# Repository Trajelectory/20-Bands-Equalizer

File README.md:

# Equalizer 20 Bands avec Vumètre LED

## Description du Projet
Ce projet permet de modifier le son en ajustant les niveaux de fréquence tout en affichant visuellement l'intensité du signal audio via un vumètre LED.

## Fonctionnalités
- **Égaliseur graphique 20 bandes** pour un réglage précis des fréquences audio.
- **Vumètre LED** basé sur un circuit spécialisé pour une visualisation dynamique du signal.
- **Entrée et sortie audio** pour intégration dans des systèmes hi-fi ou de studio.
- **Alimentation stabilisée** pour un fonctionnement optimal et sans bruit.
- **Conception optimisée** avec une séparation des pistes minimisant les interférences.

## Matériel Utilisé
- **Logiciel de conception** : KiCad
- **Composants principaux** :
  - Amplificateurs opérationnels (ex: TL074, TL072)
  - Filtres actifs RC pour le traitement du signal
  - Potentiomètres pour le réglage des bandes
  - Circuit de vumètre
  - LED pour l'affichage du signal
  - Connecteurs audio pour l'entrée/sortie

## Fichiers Inclus
- **Schéma KiCad** : `20 Bands Equalizer.kicad_sch`
- **PCB KiCad** : `20 Bands Equalizer.kicad_pcb`
- **Les fichiers de fabrications compatible JLCPCB`

## Améliorations Possibles
- Ajout d'un **affichage LCD** pour afficher les valeurs des bandes.
- Conception d'un **boîtier imprimé en 3D** pour l'intégration.
- Optimisation de l'alimentation pour **baisser la consommation énergétique**.

## Licence
Ce projet est sous licence **MIT**, ce qui signifie que vous pouvez l'utiliser, le modifier et le partager librement en mentionnant l'auteur original.

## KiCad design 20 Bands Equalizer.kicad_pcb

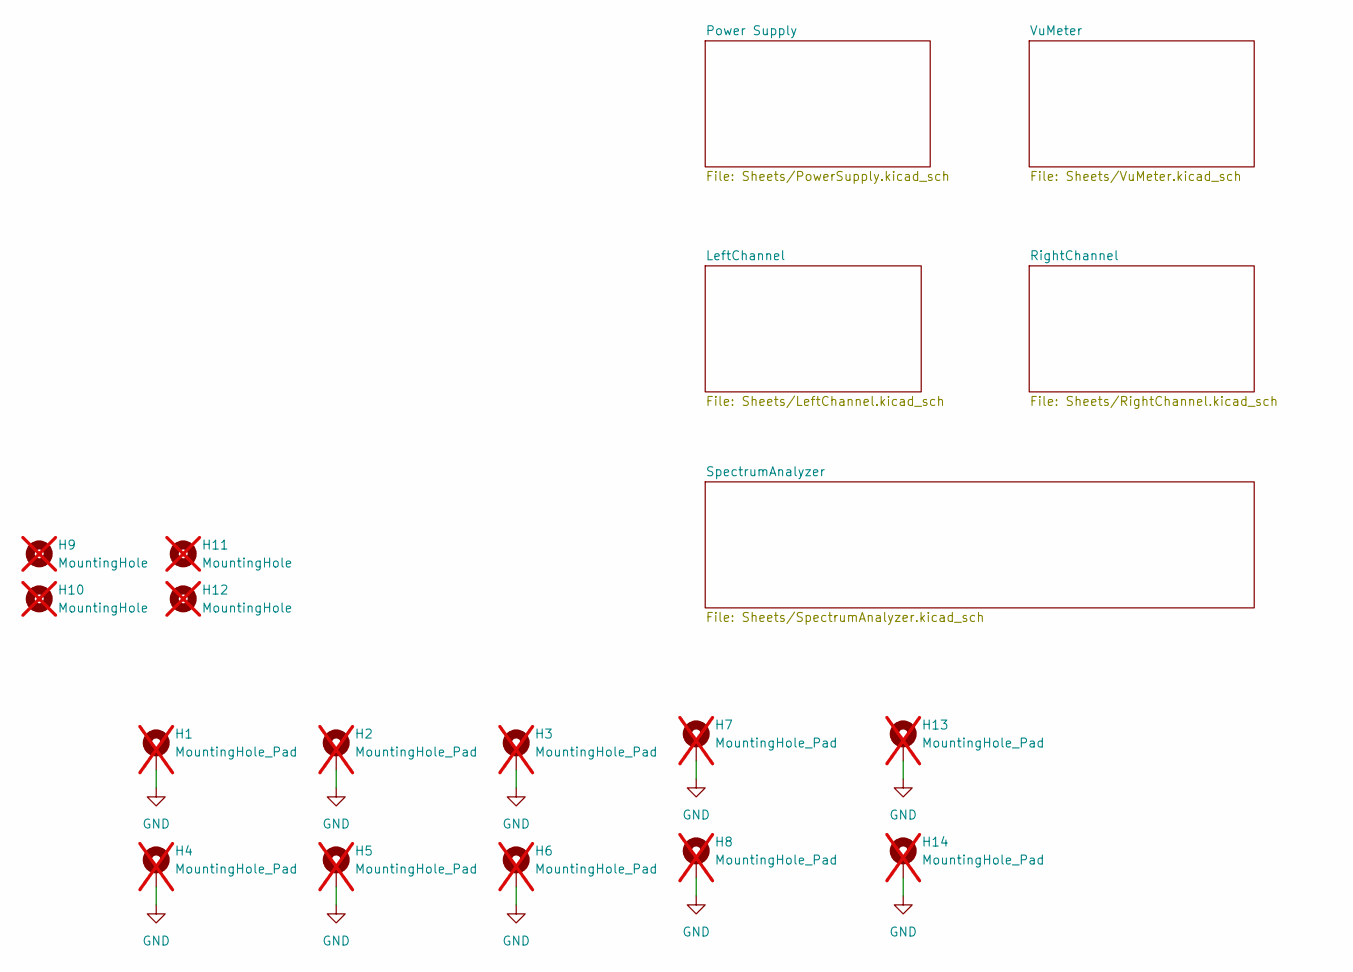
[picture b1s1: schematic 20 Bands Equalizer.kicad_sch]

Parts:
H1, H2, H3, H4, H5, H6, H7, H8, H13, H14: MountingHole_Pad; MountingHole_3.2mm_M3_Pad_Via; not fitted
H9, H10, H11, H12: MountingHole; MountingHole_2.5mm; not fitted

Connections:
0V: H1.1, H2.1, H3.1, H4.1, H5.1, H6.1, H7.1, H8.1, H13.1, H14.1; also elsewhere on the board

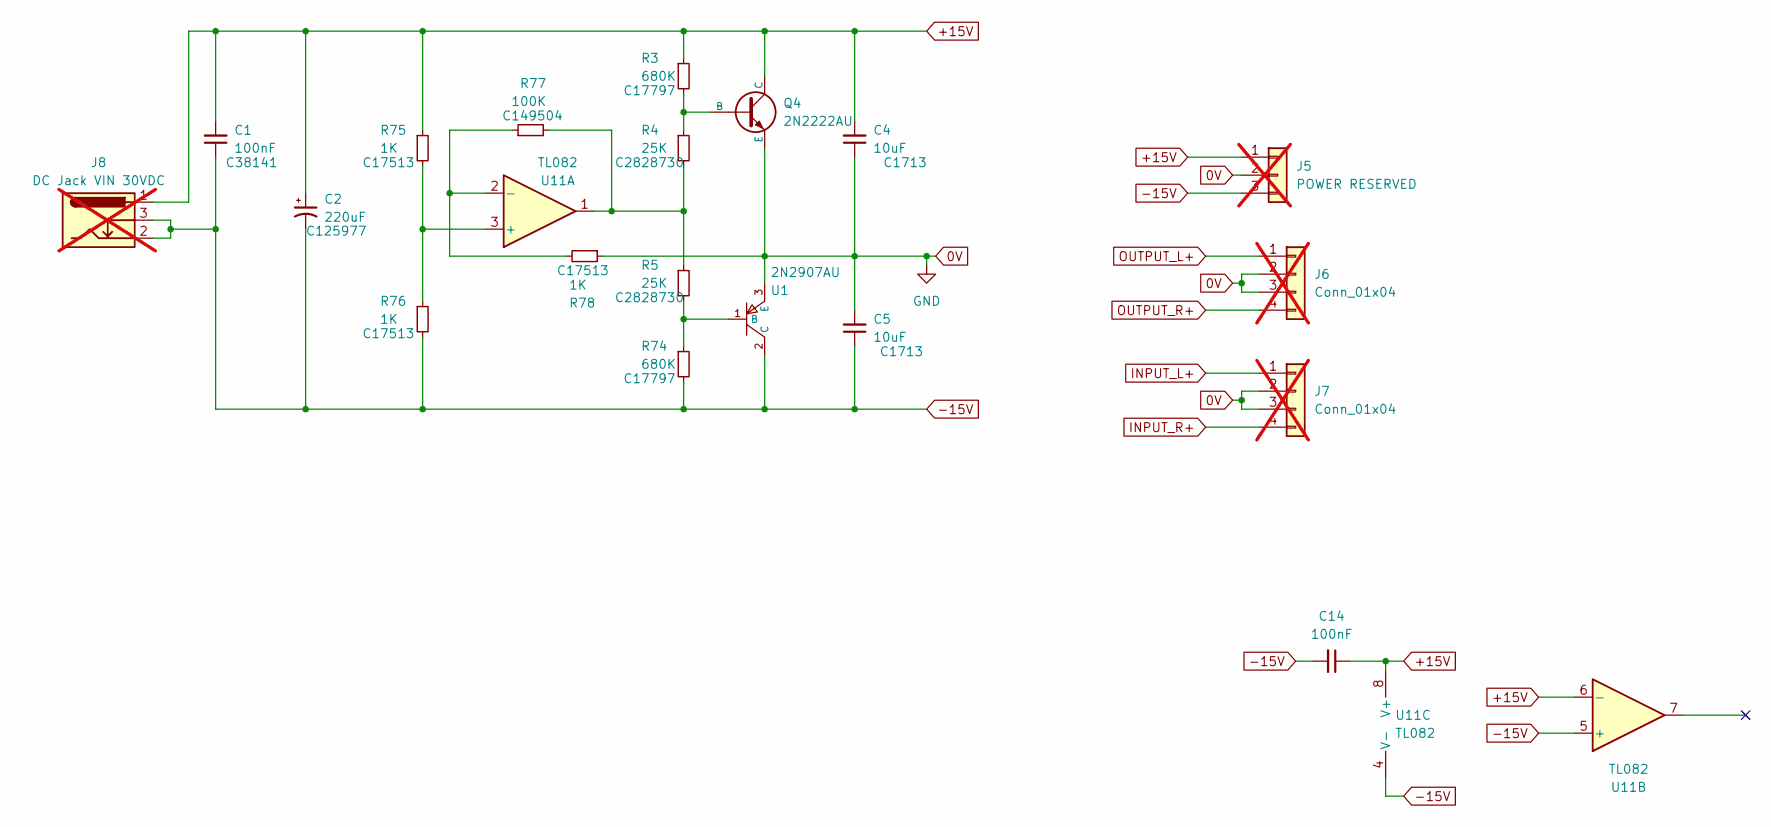
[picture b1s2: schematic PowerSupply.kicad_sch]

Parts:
C1, C14: 100nF; C_0805_2012Metric_Pad1.18x1.45mm_HandSolder; LCSC C38141
C2: 220uF; CP_Elec_10x10; LCSC C125977
C4, C5: 10uF; C_0805_2012Metric_Pad1.18x1.45mm_HandSolder; LCSC C1713
J5: POWER RESERVED; JST_XH_B3B-XH-A_1x03_P2.50mm_Vertical; not fitted
J6, J7: Conn_01x04; JST_XH_B4B-XH-A_1x04_P2.50mm_Vertical; not fitted
J8: DC Jack VIN 30VDC; BarrelJack_GCT_DCJ200-10-A_Horizontal; not fitted
Q4: 2N2222AU; SOT-89-3_L4.5-W2.4-P1.50-LS4.0-BR; LCSC C21714170
R3, R74: 680K; R_0805_2012Metric_Pad1.20x1.40mm_HandSolder; LCSC C17797
R4, R5: 25K; R_0805_2012Metric_Pad1.20x1.40mm_HandSolder; LCSC C2828730
R75, R76, R78: 1K; R_0805_2012Metric_Pad1.20x1.40mm_HandSolder; LCSC C17513
R77: 100K; R_0805_2012Metric_Pad1.20x1.40mm_HandSolder; LCSC C149504
U1: 2N2907AU; SOT-89-3_L4.5-W2.5-P1.50-LS4.2-TL; LCSC C5362129
U11: TL082; SOIC-8_3.9x4.9mm_P1.27mm; LCSC C6966

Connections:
0V: C4.1, C5.2, J5.2, J6.2, J6.3, J7.2, J7.3, Q4.3 (E), R78.1, U1.3 (E); also elsewhere on the board
+15V: C1.2, C2.1, C4.2, C14.1, J5.1, J8.1, Q4.2 (C), R3.1, R75.1, U11.6 (-), U11.8 (V+); also elsewhere on the board
-15V: C1.1, C2.2, C5.1, C14.2, J5.3, J8.2, J8.3, R74.2, R76.2, U1.2 (C), U11.4 (V-), U11.5 (+); also elsewhere on the board
INPUT_L+: J7.1; also elsewhere on the board
INPUT_R+: J7.4; also elsewhere on the board
unnamed: Q4.1 (B), R3.2, R4.1
unnamed: R4.2, R5.1, R77.2, U11.1
unnamed: R5.2, R74.1, U1.1 (B)
unnamed: R75.2, R76.1, U11.3 (+)
unnamed: R77.1, R78.2, U11.2 (-)
OUTPUT_L+: J6.1; also elsewhere on the board
OUTPUT_R+: J6.4; also elsewhere on the board

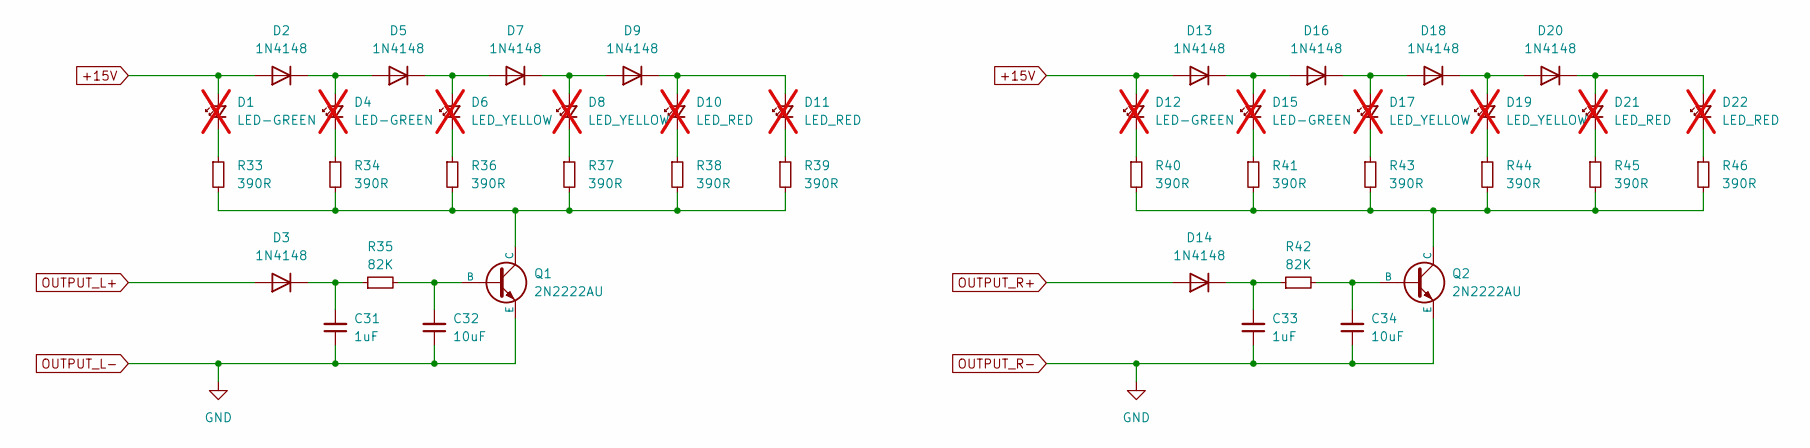
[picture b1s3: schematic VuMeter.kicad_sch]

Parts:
C31, C33: 1uF; C_0805_2012Metric_Pad1.18x1.45mm_HandSolder; LCSC C28323
C32, C34: 10uF; C_0805_2012Metric_Pad1.18x1.45mm_HandSolder; LCSC C1713
D1, D4, D12, D15: LED-GREEN; Green-ICE-CUBE-LED-5x5mm-XSCWD23MB-SunLED; LCSC C5174713; not fitted
D2, D3, D5, D7, D9, D13, D14, D16, D18, D20: 1N4148; D_SOD-123; LCSC C83528
D6, D8, D17, D19: LED_YELLOW; Orange-ICE-CUBE-LED-5x5mm-XSCWD23MB-SunLED; LCSC C5174714; not fitted
D10, D11, D21, D22: LED_RED; Red-ICE-CUBE-LED-5x5mm-XSCWD23MB-SunLED; LCSC C5174712; not fitted
Q1, Q2: 2N2222AU; SOT-89-3_L4.5-W2.4-P1.50-LS4.0-BR; LCSC C21714170
R33, R34, R36, R37, R38, R39, R40, R41, R43, R44, R45, R46: 390R; R_0805_2012Metric_Pad1.20x1.40mm_HandSolder; LCSC C17655
R35, R42: 82K; R_0805_2012Metric_Pad1.20x1.40mm_HandSolder; LCSC C17840

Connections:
0V: C31.1, C32.1, C33.1, C34.1, Q1.3 (E), Q2.3 (E); also elsewhere on the board
+15V: D1.2 (A), D2.2 (A), D12.2 (A), D13.2 (A); also elsewhere on the board
unnamed: D1.1 (K), R33.1
unnamed: D2.1 (K), D4.2 (A), D5.2 (A)
unnamed: C31.2, D3.1 (K), R35.1
unnamed: D4.1 (K), R34.1
unnamed: D5.1 (K), D6.2 (A), D7.2 (A)
unnamed: D6.1 (K), R36.1
unnamed: D7.1 (K), D8.2 (A), D9.2 (A)
unnamed: D8.1 (K), R37.1
unnamed: D9.1 (K), D10.2 (A), D11.2 (A)
unnamed: D10.1 (K), R38.1
unnamed: D11.1 (K), R39.1
unnamed: D12.1 (K), R40.1
unnamed: D13.1 (K), D15.2 (A), D16.2 (A)
unnamed: C33.2, D14.1 (K), R42.1
unnamed: D15.1 (K), R41.1
unnamed: D16.1 (K), D17.2 (A), D18.2 (A)
unnamed: D17.1 (K), R43.1
unnamed: D18.1 (K), D19.2 (A), D20.2 (A)
unnamed: D19.1 (K), R44.1
unnamed: D20.1 (K), D21.2 (A), D22.2 (A)
unnamed: D21.1 (K), R45.1
unnamed: D22.1 (K), R46.1
unnamed: C32.2, Q1.1 (B), R35.2
unnamed: Q1.2 (C), R33.2, R34.2, R36.2, R37.2, R38.2, R39.2
unnamed: C34.2, Q2.1 (B), R42.2
unnamed: Q2.2 (C), R40.2, R41.2, R43.2, R44.2, R45.2, R46.2
OUTPUT_L+: D3.2 (A); also elsewhere on the board
OUTPUT_R+: D14.2 (A); also elsewhere on the board

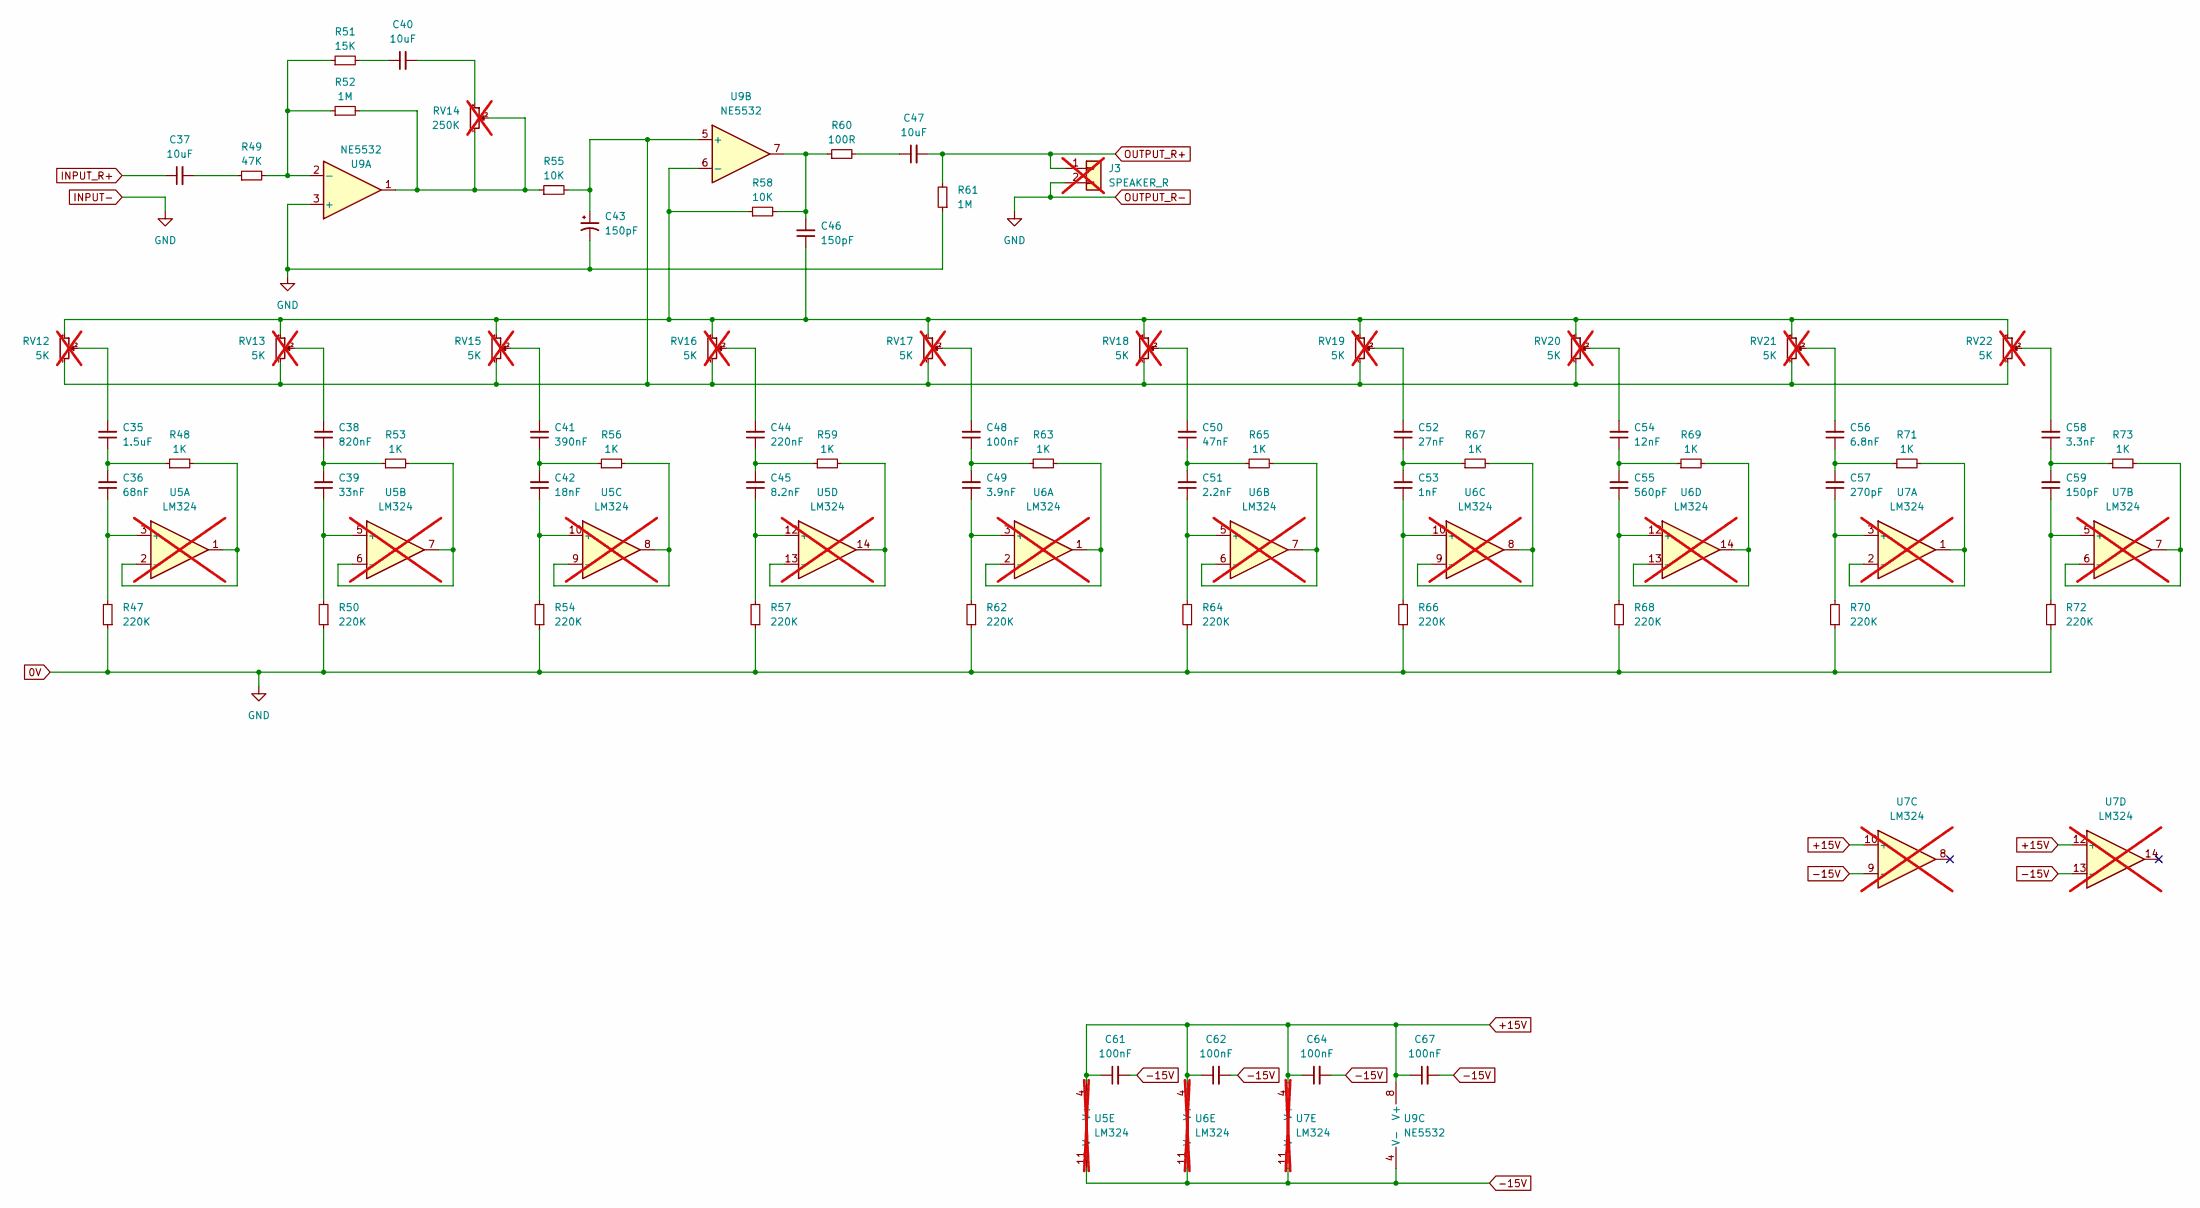
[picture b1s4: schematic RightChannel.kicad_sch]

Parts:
C35: 1.5uF; C_0805_2012Metric_Pad1.18x1.45mm_HandSolder; LCSC C6266893
C36: 68nF; C_0805_2012Metric_Pad1.18x1.45mm_HandSolder; LCSC C107159
C37, C40, C47: 10uF; C_0805_2012Metric_Pad1.18x1.45mm_HandSolder; LCSC C1713
C38: 820nF; C_0805_2012Metric_Pad1.18x1.45mm_HandSolder; LCSC C67958
C39: 33nF; C_0805_2012Metric_Pad1.18x1.45mm_HandSolder; LCSC C344201
C41: 390nF; C_0805_2012Metric_Pad1.18x1.45mm_HandSolder; LCSC C841545
C42: 18nF; C_0805_2012Metric_Pad1.18x1.45mm_HandSolder; LCSC C5186912
C43, C46, C59: 150pF; C_0805_2012Metric_Pad1.18x1.45mm_HandSolder; LCSC C107111
C44: 220nF; C_0805_2012Metric_Pad1.18x1.45mm_HandSolder; LCSC C6119934
C45: 8.2nF; C_0805_2012Metric_Pad1.18x1.45mm_HandSolder; LCSC C5186918
C48, C61, C62, C64, C67: 100nF; C_0805_2012Metric_Pad1.18x1.45mm_HandSolder; LCSC C38141
C49: 3.9nF; C_0805_2012Metric_Pad1.18x1.45mm_HandSolder; LCSC C97901
C50: 47nF; C_0805_2012Metric_Pad1.18x1.45mm_HandSolder; LCSC C107154
C51: 2.2nF; C_0805_2012Metric_Pad1.18x1.45mm_HandSolder; LCSC C36576
C52: 27nF; C_0805_2012Metric_Pad1.18x1.45mm_HandSolder; LCSC C520042
C53: 1nF; C_0805_2012Metric_Pad1.18x1.45mm_HandSolder; LCSC C94121
C54: 12nF; C_0805_2012Metric_Pad1.18x1.45mm_HandSolder; LCSC C38141
C55: 560pF; C_0805_2012Metric_Pad1.18x1.45mm_HandSolder; LCSC C107119
C56: 6.8nF; C_0805_2012Metric_Pad1.18x1.45mm_HandSolder; LCSC C1755
C57: 270pF; C_0805_2012Metric_Pad1.18x1.45mm_HandSolder; LCSC C113828
C58: 3.3nF; C_0805_2012Metric_Pad1.18x1.45mm_HandSolder; LCSC C7467177
J3: SPEAKER_R; JST_XH_S2B-XH-A-1_1x02_P2.50mm_Horizontal; not fitted
R47, R50, R54, R57, R62, R64, R66, R68, R70, R72: 220K; R_0805_2012Metric_Pad1.20x1.40mm_HandSolder; LCSC C17556
R48, R53, R56, R59, R63, R65, R67, R69, R71, R73: 1K; R_0805_2012Metric_Pad1.20x1.40mm_HandSolder; LCSC C17513
R49: 47K; R_0805_2012Metric_Pad1.20x1.40mm_HandSolder; LCSC C102018
R51: 15K; R_0805_2012Metric_Pad1.20x1.40mm_HandSolder; LCSC C17475
R52, R61: 1M; R_0805_2012Metric_Pad1.20x1.40mm_HandSolder; LCSC C17514
R55, R58: 10K; R_0805_2012Metric_Pad1.20x1.40mm_HandSolder; LCSC C17414
R60: 100R; R_0805_2012Metric_Pad1.20x1.40mm_HandSolder; LCSC C17408
RV12, RV13, RV15, RV16, RV17, RV18, RV19, RV20, RV21, RV22: 5K; Potentiometer_Bourns_PTA3043_Single_Slide; LCSC 652-PTA30432015CPB50; not fitted
RV14: 250K; Potentiometer_Bourns_PTA2043_Single_Slide; LCSC 652-PTA2432010CIB254; not fitted
U5, U6, U7: LM324; DIP-14_W7.62mm_LongPads; not fitted
U9: NE5532; SOIC-8_3.9x4.9mm_P1.27mm; LCSC C7426

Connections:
0V: C43.2, J3.2, R47.1, R50.1, R54.1, R57.1, R61.1, R62.1, R64.1, R66.1, R68.1, R70.1, R72.1, U9.3 (+); also elsewhere on the board
+15V: C61.1, C62.1, C64.1, C67.1, U5.4 (V+), U6.4 (V+), U7.4 (V+), U7.10 (+), U7.12 (+), U9.8 (V+); also elsewhere on the board
-15V: C61.2, C62.2, C64.2, C67.2, U5.11 (V-), U6.11 (V-), U7.9 (-), U7.11 (V-), U7.13 (-), U9.4 (V-); also elsewhere on the board
INPUT_R+: C37.1; also elsewhere on the board
unnamed: C35.1, C36.2, R48.1
unnamed: C35.2, RV12.2
unnamed: C37.2, R49.1
unnamed: C38.1, C39.2, R53.1
unnamed: C38.2, RV13.2
unnamed: C40.1, R51.2
unnamed: C40.2, RV14.1
unnamed: C41.1, C42.2, R56.1
unnamed: C41.2, RV15.2
unnamed: C44.1, C45.2, R59.1
unnamed: C44.2, RV16.2
unnamed: C46.2, R58.2, R60.1, U9.7
unnamed: C47.1, R60.2
unnamed: C48.1, C49.2, R63.1
unnamed: C48.2, RV17.2
unnamed: C50.1, C51.2, R65.1
unnamed: C50.2, RV18.2
unnamed: C52.1, C53.2, R67.1
unnamed: C52.2, RV19.2
unnamed: C54.1, C55.2, R69.1
unnamed: C54.2, RV20.2
unnamed: C56.1, C57.2, R71.1
unnamed: C56.2, RV21.2
unnamed: C58.1, C59.2, R73.1
unnamed: C58.2, RV22.2
unnamed: R52.2, R55.1, RV14.2, RV14.3, U9.1
unnamed: C36.1, R47.2, U5.3 (+)
unnamed: R48.2, U5.1, U5.2 (-)
unnamed: C39.1, R50.2, U5.5 (+)
unnamed: R53.2, U5.6 (-), U5.7
unnamed: C42.1, R54.2, U5.10 (+)
unnamed: R56.2, U5.8, U5.9 (-)
unnamed: C45.1, R57.2, U5.12 (+)
unnamed: R59.2, U5.13 (-), U5.14
unnamed: C49.1, R62.2, U6.3 (+)
unnamed: R63.2, U6.1, U6.2 (-)
unnamed: C51.1, R64.2, U6.5 (+)
unnamed: R65.2, U6.6 (-), U6.7
unnamed: C53.1, R66.2, U6.10 (+)
unnamed: R67.2, U6.8, U6.9 (-)
unnamed: C55.1, R68.2, U6.12 (+)
unnamed: R69.2, U6.13 (-), U6.14
unnamed: C57.1, R70.2, U7.3 (+)
unnamed: R71.2, U7.1, U7.2 (-)
unnamed: C59.1, R72.2, U7.5 (+)
unnamed: R73.2, U7.6 (-), U7.7
unnamed: R49.2, R51.1, R52.1, U9.2 (-)
unnamed: C43.1, R55.2, RV12.3, RV13.3, RV15.3, RV16.3, RV17.3, RV18.3, RV19.3, RV20.3, RV21.3, RV22.3, U9.5 (+)
unnamed: C46.1, R58.1, RV12.1, RV13.1, RV15.1, RV16.1, RV17.1, RV18.1, RV19.1, RV20.1, RV21.1, RV22.1, U9.6 (-)
OUTPUT_R+: C47.2, J3.1, R61.2; also elsewhere on the board

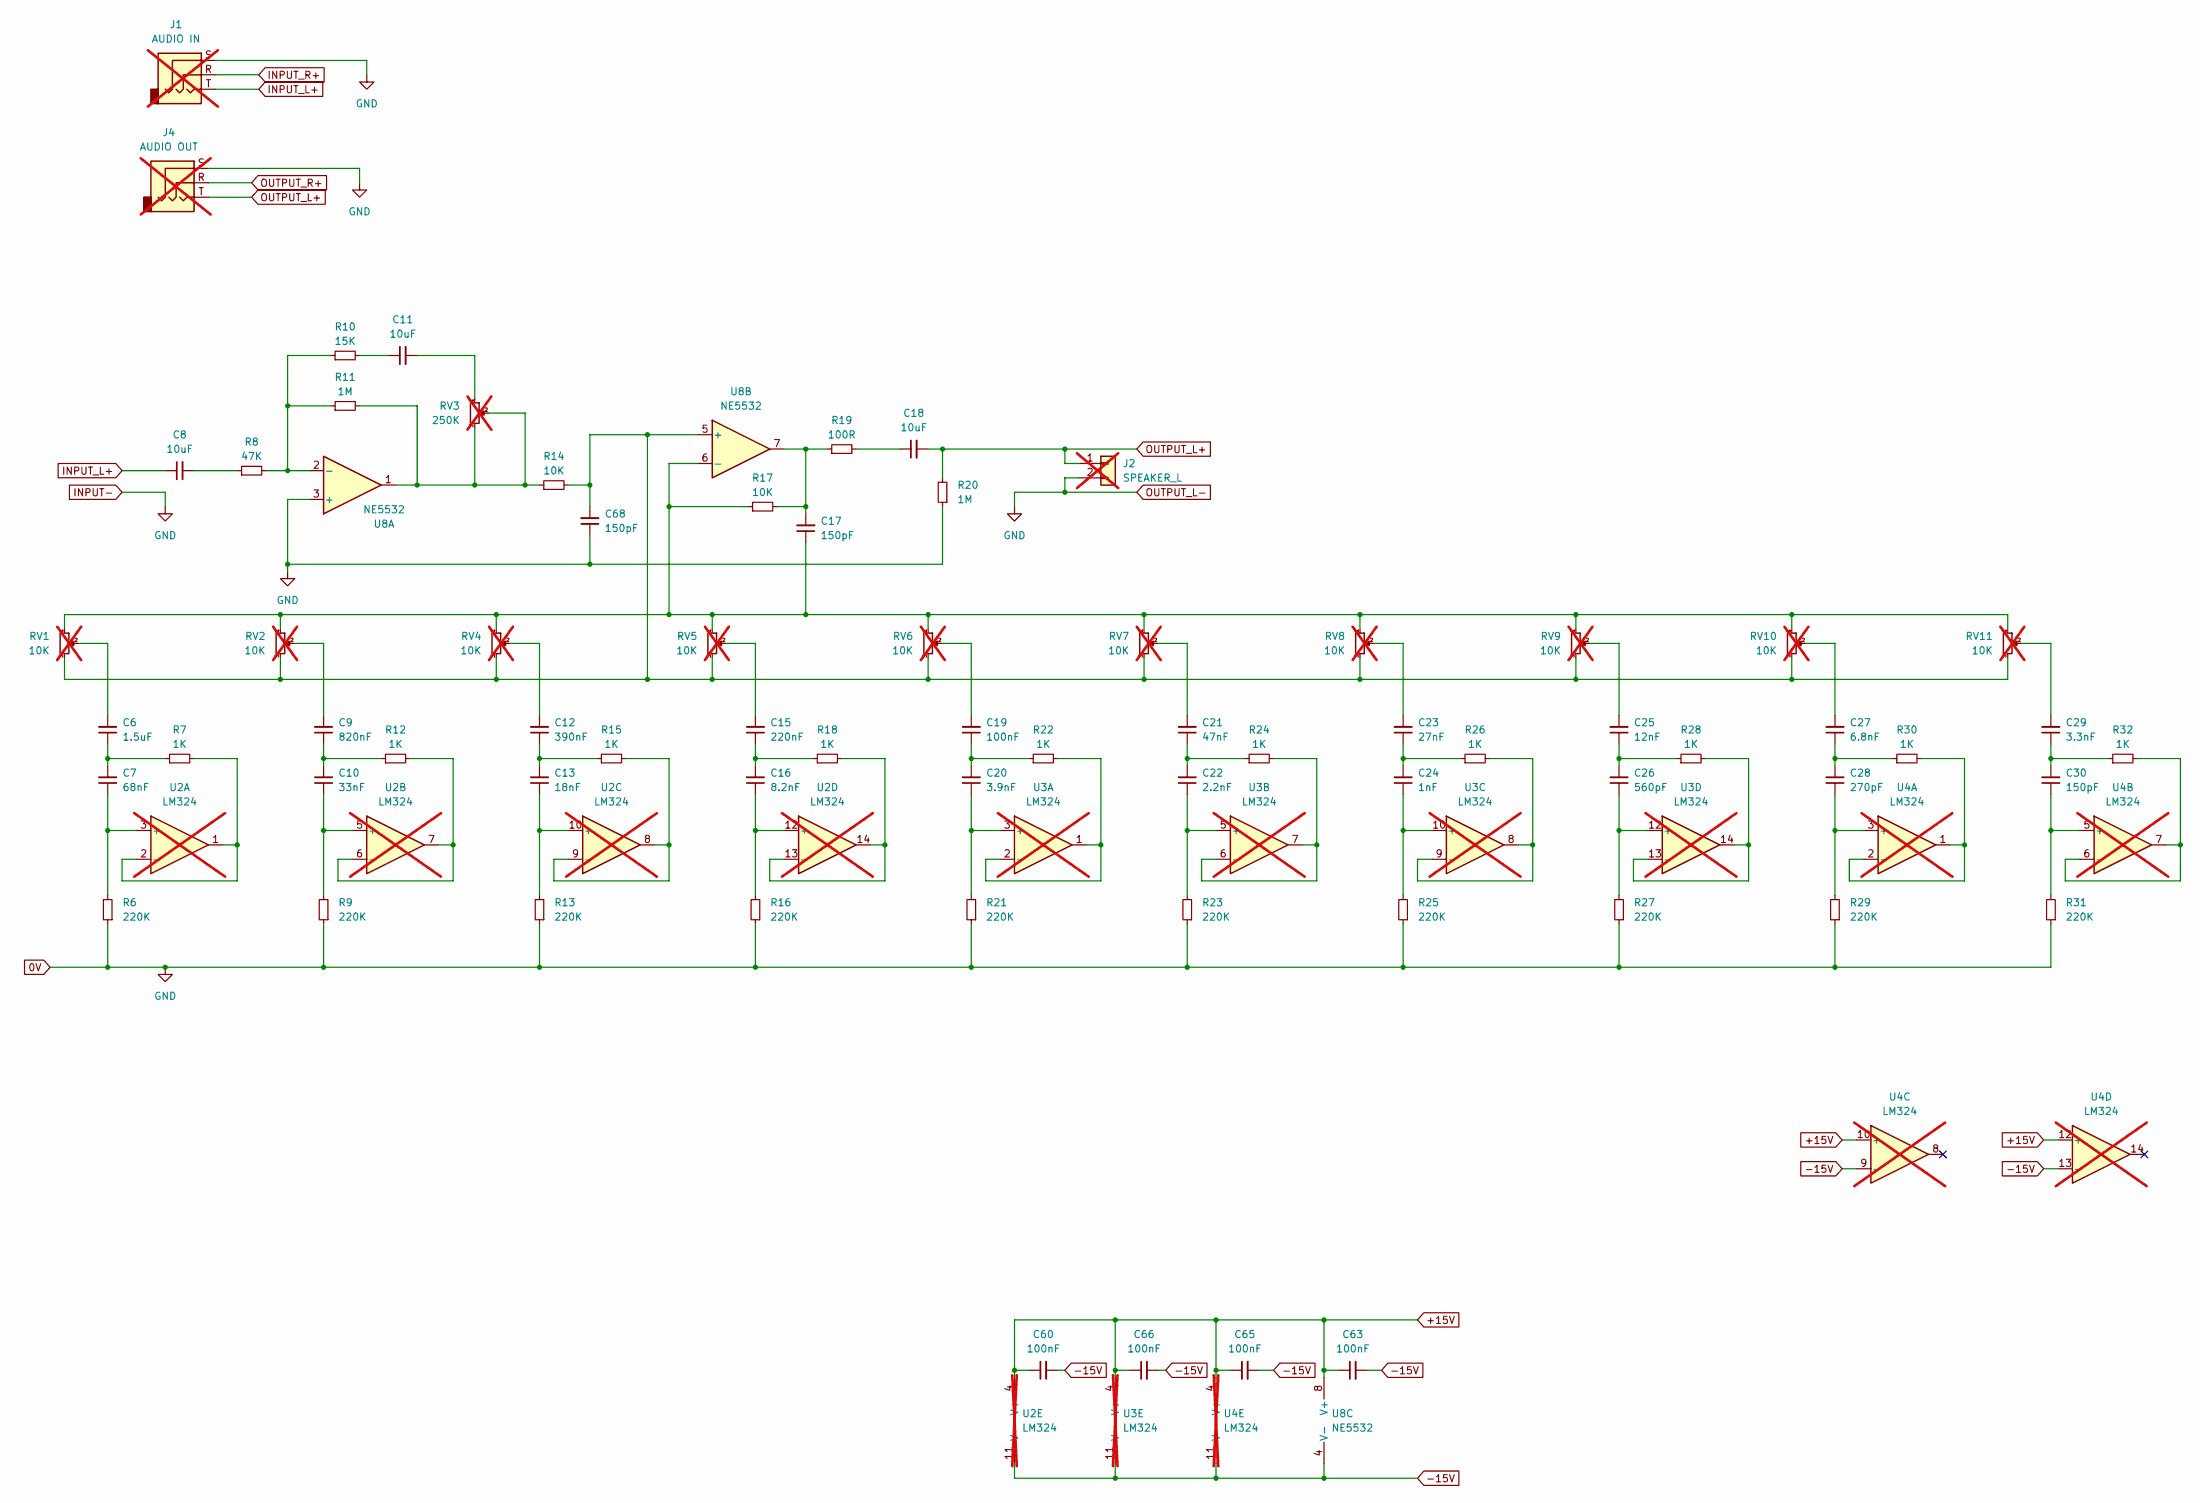
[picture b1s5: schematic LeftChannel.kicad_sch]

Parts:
C6: 1.5uF; C_0805_2012Metric_Pad1.18x1.45mm_HandSolder; LCSC C6266893
C7: 68nF; C_0805_2012Metric_Pad1.18x1.45mm_HandSolder; LCSC C107159
C8, C11, C18: 10uF; C_0805_2012Metric_Pad1.18x1.45mm_HandSolder; LCSC C1713
C9: 820nF; C_0805_2012Metric_Pad1.18x1.45mm_HandSolder; LCSC C67958
C10: 33nF; C_0805_2012Metric_Pad1.18x1.45mm_HandSolder; LCSC C344201
C12: 390nF; C_0805_2012Metric_Pad1.18x1.45mm_HandSolder; LCSC C841545
C13: 18nF; C_0805_2012Metric_Pad1.18x1.45mm_HandSolder; LCSC C5186912
C15: 220nF; C_0805_2012Metric_Pad1.18x1.45mm_HandSolder; LCSC C6119934
C16: 8.2nF; C_0805_2012Metric_Pad1.18x1.45mm_HandSolder; LCSC C5186918
C17, C30, C68: 150pF; C_0805_2012Metric_Pad1.18x1.45mm_HandSolder; LCSC C107111
C19, C60, C63, C65, C66: 100nF; C_0805_2012Metric_Pad1.18x1.45mm_HandSolder; LCSC C38141
C20: 3.9nF; C_0805_2012Metric_Pad1.18x1.45mm_HandSolder; LCSC C97901
C21: 47nF; C_0805_2012Metric_Pad1.18x1.45mm_HandSolder; LCSC C107154
C22: 2.2nF; C_0805_2012Metric_Pad1.18x1.45mm_HandSolder; LCSC C36576
C23: 27nF; C_0805_2012Metric_Pad1.18x1.45mm_HandSolder; LCSC C520042
C24: 1nF; C_0805_2012Metric_Pad1.18x1.45mm_HandSolder; LCSC C94121
C25: 12nF; C_0805_2012Metric_Pad1.18x1.45mm_HandSolder; LCSC C38141
C26: 560pF; C_0805_2012Metric_Pad1.18x1.45mm_HandSolder; LCSC C107119
C27: 6.8nF; C_0805_2012Metric_Pad1.18x1.45mm_HandSolder; LCSC C1755
C28: 270pF; C_0805_2012Metric_Pad1.18x1.45mm_HandSolder; LCSC C113828
C29: 3.3nF; C_0805_2012Metric_Pad1.18x1.45mm_HandSolder; LCSC C7467177
J1: AUDIO IN; Jack_3.5mm_CUI_SJ1-3523N_Horizontal; not fitted
J2: SPEAKER_L; JST_XH_S2B-XH-A-1_1x02_P2.50mm_Horizontal; not fitted
J4: AUDIO OUT; Jack_3.5mm_CUI_SJ1-3523N_Horizontal; not fitted
R6, R9, R13, R16, R21, R23, R25, R27, R29, R31: 220K; R_0805_2012Metric_Pad1.20x1.40mm_HandSolder; LCSC C17556
R7, R12, R15, R18, R22, R24, R26, R28, R30, R32: 1K; R_0805_2012Metric_Pad1.20x1.40mm_HandSolder; LCSC C17513
R8: 47K; R_0805_2012Metric_Pad1.20x1.40mm_HandSolder; LCSC C102018
R10: 15K; R_0805_2012Metric_Pad1.20x1.40mm_HandSolder; LCSC C17475
R11, R20: 1M; R_0805_2012Metric_Pad1.20x1.40mm_HandSolder; LCSC C17514
R14, R17: 10K; R_0805_2012Metric_Pad1.20x1.40mm_HandSolder; LCSC C17414
R19: 100R; R_0805_2012Metric_Pad1.20x1.40mm_HandSolder; LCSC C17408
RV1, RV2, RV4, RV5, RV6, RV7, RV8, RV9, RV10, RV11: 10K; Potentiometer_Bourns_PTA3043_Single_Slide; not fitted
RV3: 250K; Potentiometer_Bourns_PTA2043_Single_Slide; LCSC 652-PTA2432010CIB254; not fitted
U2, U3, U4: LM324; DIP-14_W7.62mm_LongPads; not fitted
U8: NE5532; SOIC-8_3.9x4.9mm_P1.27mm; LCSC C7426

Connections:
0V: C68.1, J1.S, J2.2, J4.S, R6.1, R9.1, R13.1, R16.1, R20.1, R21.1, R23.1, R25.1, R27.1, R29.1, R31.1, U8.3 (+); also elsewhere on the board
+15V: C60.1, C63.1, C65.1, C66.1, U2.4 (V+), U3.4 (V+), U4.4 (V+), U4.10 (+), U4.12 (+), U8.8 (V+); also elsewhere on the board
-15V: C60.2, C63.2, C65.2, C66.2, U2.11 (V-), U3.11 (V-), U4.9 (-), U4.11 (V-), U4.13 (-), U8.4 (V-); also elsewhere on the board
INPUT_L+: C8.1, J1.T; also elsewhere on the board
INPUT_R+: J1.R; also elsewhere on the board
unnamed: C6.1, C7.2, R7.1
unnamed: C6.2, RV1.2
unnamed: C8.2, R8.1
unnamed: C9.2, RV2.2
unnamed: C9.1, C10.2, R12.1
unnamed: C11.1, R10.2
unnamed: C11.2, RV3.1
unnamed: C12.1, C13.2, R15.1
unnamed: C12.2, RV4.2
unnamed: C15.1, C16.2, R18.1
unnamed: C15.2, RV5.2
unnamed: C17.2, R17.2, R19.1, U8.7
unnamed: C18.1, R19.2
unnamed: C19.1, C20.2, R22.1
unnamed: C19.2, RV6.2
unnamed: C21.1, C22.2, R24.1
unnamed: C21.2, RV7.2
unnamed: C23.1, C24.2, R26.1
unnamed: C23.2, RV8.2
unnamed: C25.1, C26.2, R28.1
unnamed: C25.2, RV9.2
unnamed: C27.1, C28.2, R30.1
unnamed: C27.2, RV10.2
unnamed: C29.1, C30.2, R32.1
unnamed: C29.2, RV11.2
unnamed: R11.2, R14.1, RV3.2, RV3.3, U8.1
unnamed: C7.1, R6.2, U2.3 (+)
unnamed: R7.2, U2.1, U2.2 (-)
unnamed: C10.1, R9.2, U2.5 (+)
unnamed: R12.2, U2.6 (-), U2.7
unnamed: C13.1, R13.2, U2.10 (+)
unnamed: R15.2, U2.8, U2.9 (-)
unnamed: C16.1, R16.2, U2.12 (+)
unnamed: R18.2, U2.13 (-), U2.14
unnamed: C20.1, R21.2, U3.3 (+)
unnamed: R22.2, U3.1, U3.2 (-)
unnamed: C22.1, R23.2, U3.5 (+)
unnamed: R24.2, U3.6 (-), U3.7
unnamed: C24.1, R25.2, U3.10 (+)
unnamed: R26.2, U3.8, U3.9 (-)
unnamed: C26.1, R27.2, U3.12 (+)
unnamed: R28.2, U3.13 (-), U3.14
unnamed: C28.1, R29.2, U4.3 (+)
unnamed: R30.2, U4.1, U4.2 (-)
unnamed: C30.1, R31.2, U4.5 (+)
unnamed: R32.2, U4.6 (-), U4.7
unnamed: R8.2, R10.1, R11.1, U8.2 (-)
unnamed: C68.2, R14.2, RV1.3, RV2.3, RV4.3, RV5.3, RV6.3, RV7.3, RV8.3, RV9.3, RV10.3, RV11.3, U8.5 (+)
unnamed: C17.1, R17.1, RV1.1, RV2.1, RV4.1, RV5.1, RV6.1, RV7.1, RV8.1, RV9.1, RV10.1, RV11.1, U8.6 (-)
OUTPUT_L+: C18.2, J2.1, J4.T, R20.2; also elsewhere on the board
OUTPUT_R+: J4.R; also elsewhere on the board

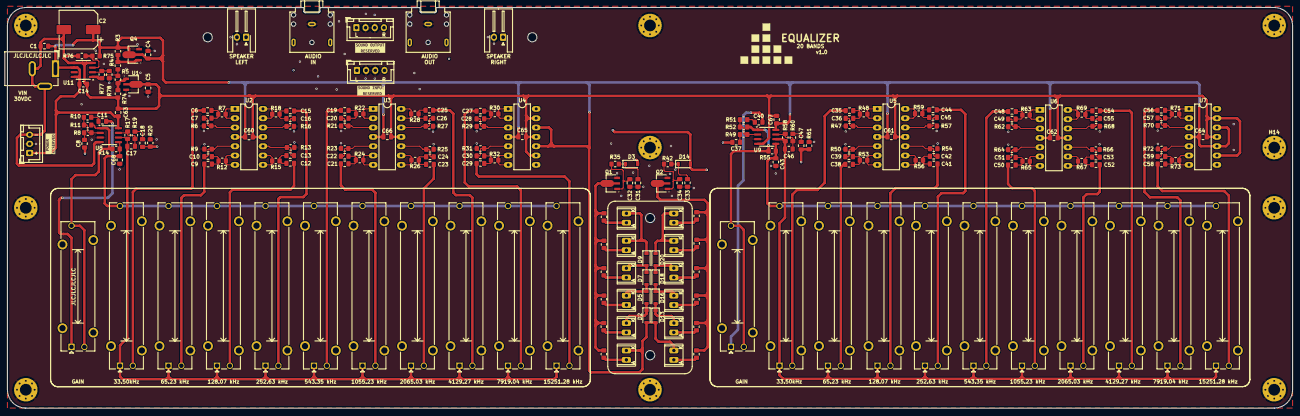
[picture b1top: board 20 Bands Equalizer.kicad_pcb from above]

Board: 4 copper layers, 349.9 x 109.0 mm, 225 parts (0 on the bottom side), 136 nets.

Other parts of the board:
kibuzzard-677A2DA0: G***; kibuzzard-677A2DA0
kibuzzard-679F2E4A: G***; kibuzzard-679F2E4A
kibuzzard-679F2EA5: G***; kibuzzard-679F2EA5

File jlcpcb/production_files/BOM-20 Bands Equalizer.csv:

Comment,Designator,Footprint,LCSC,Quantity
220nF,"C15,C44",C_0805_2012Metric_Pad1.18x1.45mm_HandSolder,C107131,2
33nF,"C10,C39",C_0805_2012Metric_Pad1.18x1.45mm_HandSolder,C107150,2
68nF,"C36,C7",C_0805_2012Metric_Pad1.18x1.45mm_HandSolder,C107159,2
1M,"R11,R20,R52,R61",R_0805_2012Metric_Pad1.20x1.40mm_HandSolder,C107700,4
270pF,"C28,C57",C_0805_2012Metric_Pad1.18x1.45mm_HandSolder,C113858,2
390R,"R33,R34,R36,R37,R38,R39,R40,R41,R43,R44,R45,R46",R_0805_2012Metric_Pad1.20x1.40mm_HandSolder,C114543,12
220uF,C2,CP_Elec_10x10,C125977,1
10uF,C32,C_0805_2012Metric_Pad1.18x1.45mm_HandSolder,C1713,1
12nF,"C25,C54",C_0805_2012Metric_Pad1.18x1.45mm_HandSolder,C1715,2
150pF,"C30,C43,C59,C68",C_0805_2012Metric_Pad1.18x1.45mm_HandSolder,C1716,4
10K,"R14,R17,R55,R58",R_0805_2012Metric_Pad1.20x1.40mm_HandSolder,C17414,4
3.9nF,"C20,C49",C_0805_2012Metric_Pad1.18x1.45mm_HandSolder,C1742,2
47nF,"C21,C50",C_0805_2012Metric_Pad1.18x1.45mm_HandSolder,C1745,2
15K,"R10,R51",R_0805_2012Metric_Pad1.20x1.40mm_HandSolder,C17475,2
6.8nF,"C27,C56",C_0805_2012Metric_Pad1.18x1.45mm_HandSolder,C1755,2
220K,"R13,R16,R21,R23,R25,R27,R29,R31,R47,R50,R54,R57,R6,R62,R64,R66,R68,R70,R72,R9",R_0805_2012Metric_Pad1.20x1.40mm_HandSolder,C17556,20
680K,"R3,R4,R5,R74,R75,R76,R77,R78",R_0805_2012Metric_Pad1.20x1.40mm_HandSolder,C17560,8
8.2nF,"C16,C45",C_0805_2012Metric_Pad1.18x1.45mm_HandSolder,C1758,2
47K,"R49,R8",R_0805_2012Metric_Pad1.20x1.40mm_HandSolder,C17713,2
82K,"R35,R42",R_0805_2012Metric_Pad1.20x1.40mm_HandSolder,C17840,2
560pF,"C26,C55",C_0805_2012Metric_Pad1.18x1.45mm_HandSolder,C1829,2
390nF,"C12,C41",C_0805_2012Metric_Pad1.18x1.45mm_HandSolder,C1854267,2
1uF,"C31,C33",C_0805_2012Metric_Pad1.18x1.45mm_HandSolder,C215803,2
2N2222AU,"Q1,Q2,Q4",SOT-89-3_L4.5-W2.4-P1.50-LS4.0-BR,C21714170,3
100R,"R19,R60",R_0805_2012Metric_Pad1.20x1.40mm_HandSolder,C25277,2
1K,"R12,R15,R18,R22,R24,R26,R28,R30,R32,R48,R53,R56,R59,R63,R65,R67,R69,R7,R71,R73",R_0805_2012Metric_Pad1.20x1.40mm_HandSolder,C25623,20
2.2nF,"C22,C51",C_0805_2012Metric_Pad1.18x1.45mm_HandSolder,C28260,2
10uF,"C4,C5",C_0805_2012Metric_Pad1.18x1.45mm_HandSolder,C440198,2
100nF,"C1,C11,C14,C17,C18,C19,C34,C37,C40,C46,C47,C48,C60,C61,C62,C63,C64,C65,C66,C67,C8",C_0805_2012Metric_Pad1.18x1.45mm_HandSolder,C476766,21
LED_RED,"D11,D22",Red-ICE-CUBE-LED-5x5mm-XSCWD23MB-SunLED,C5174712,2
LED-GREEN,"D12,D4",Green-ICE-CUBE-LED-5x5mm-XSCWD23MB-SunLED,C5174713,2
LED_YELLOW,"D19,D8",Orange-ICE-CUBE-LED-5x5mm-XSCWD23MB-SunLED,C5174714,2
18nF,"C13,C42",C_0805_2012Metric_Pad1.18x1.45mm_HandSolder,C5186912,2
27nF,"C23,C52",C_0805_2012Metric_Pad1.18x1.45mm_HandSolder,C520042,2
2N2907AU,U1,SOT-89-3_L4.5-W2.5-P1.50-LS4.2-TL,C5362129,1
1.5uF,"C35,C6",C_0805_2012Metric_Pad1.18x1.45mm_HandSolder,C6266893,2
820nF,"C38,C9",C_0805_2012Metric_Pad1.18x1.45mm_HandSolder,C67958,2
TL082,U11,SOIC-8_3.9x4.9mm_P1.27mm,C6966,1
NE5532,"U8,U9",SOIC-8_3.9x4.9mm_P1.27mm,C7426,2
3.3nF,"C29,C58",C_0805_2012Metric_Pad1.18x1.45mm_HandSolder,C7467177,2
1N4148,"D13,D14,D16,D18,D2,D20,D3,D5,D7,D9",D_SOD-123,C83528,10
1nF,"C24,C53",C_0805_2012Metric_Pad1.18x1.45mm_HandSolder,C94121,2
5K,,Potentiometer_Bourns_PTA3043_Single_Slide,,0
10K,,Potentiometer_Bourns_PTA3043_Single_Slide,,0
LM324,,DIP-14_W7.62mm_LongPads,,0
250K,,Potentiometer_Bourns_PTA2043_Single_Slide,,0
AUDIO OUT,,Jack_3.5mm_CUI_SJ1-3523N_Horizontal,,0
LM324,,DIP-14_W7.62mm_LongPads,,0
5K,,Potentiometer_Bourns_PTA3043_Single_Slide,,0
250K,,Potentiometer_Bourns_PTA2043_Single_Slide,,0
5K,,Potentiometer_Bourns_PTA3043_Single_Slide,,0
LM324,,DIP-14_W7.62mm_LongPads,,0
SPEAKER_R,,JST_XH_S2B-XH-A-1_1x02_P2.50mm_Horizontal,,0
5K,,Potentiometer_Bourns_PTA3043_Single_Slide,,0
10K,,Potentiometer_Bourns_PTA3043_Single_Slide,,0
10K,,Potentiometer_Bourns_PTA3043_Single_Slide,,0
10K,,Potentiometer_Bourns_PTA3043_Single_Slide,,0
5K,,Potentiometer_Bourns_PTA3043_Single_Slide,,0
5K,,Potentiometer_Bourns_PTA3043_Single_Slide,,0
10K,,Potentiometer_Bourns_PTA3043_Single_Slide,,0
10K,,Potentiometer_Bourns_PTA3043_Single_Slide,,0
LM324,,DIP-14_W7.62mm_LongPads,,0
10K,,Potentiometer_Bourns_PTA3043_Single_Slide,,0
5K,,Potentiometer_Bourns_PTA3043_Single_Slide,,0
SPEAKER_L,,JST_XH_S2B-XH-A-1_1x02_P2.50mm_Horizontal,,0
LM324,,DIP-14_W7.62mm_LongPads,,0
DC Jack VIN 30VDC,,BarrelJack_GCT_DCJ200-10-A_Horizontal,,0
AUDIO IN,,Jack_3.5mm_CUI_SJ1-3523N_Horizontal,,0
LM324,,DIP-14_W7.62mm_LongPads,,0
10K,,Potentiometer_Bourns_PTA3043_Single_Slide,,0
10K,,Potentiometer_Bourns_PTA3043_Single_Slide,,0
5K,,Potentiometer_Bourns_PTA3043_Single_Slide,,0
10K,,Potentiometer_Bourns_PTA3043_Single_Slide,,0
5K,,Potentiometer_Bourns_PTA3043_Single_Slide,,0
5K,,Potentiometer_Bourns_PTA3043_Single_Slide,,0
